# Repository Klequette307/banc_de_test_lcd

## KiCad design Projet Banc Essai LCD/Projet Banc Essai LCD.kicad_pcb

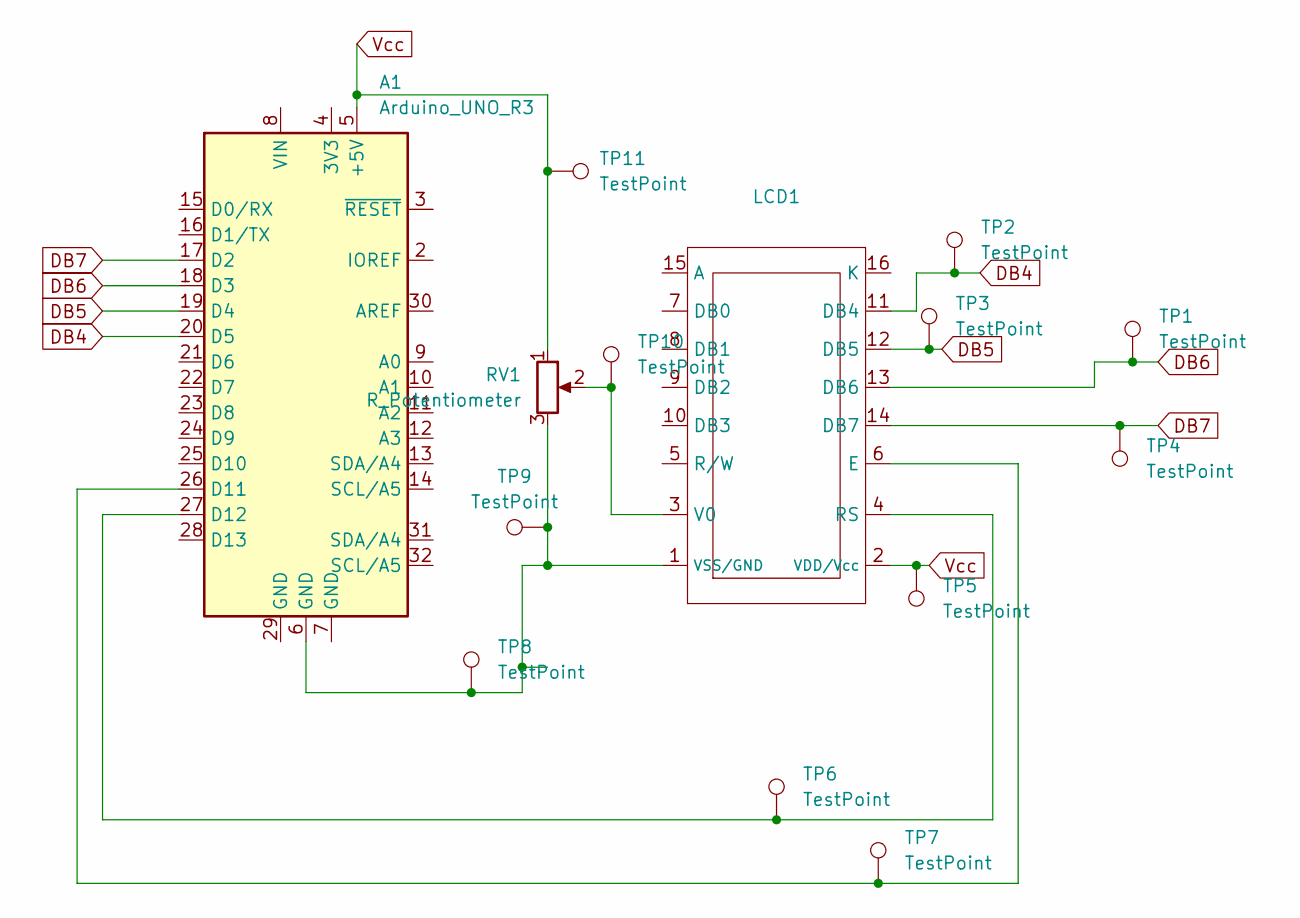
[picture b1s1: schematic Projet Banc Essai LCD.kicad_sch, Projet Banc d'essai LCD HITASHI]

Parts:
A1: Arduino_UNO_R3; Arduino_UNO_R3_WithMountingHoles
LCD1: ecran_hitachi_lcd
RV1: R_Potentiometer; Potentiometer_ACP_CA9-V10_Vertical
TP1, TP2, TP3, TP4, TP5, TP6, TP7, TP8, TP9, TP10, TP11: TestPoint; PinHeader_1x01_P1.00mm_Vertical

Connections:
DB4: A1.20 (D5), LCD1.11 (DB4), TP2.1
DB5: A1.19 (D4), LCD1.12 (DB5), TP3.1
DB6: A1.18 (D3), LCD1.13 (DB6), TP1.1
DB7: A1.17 (D2), LCD1.14 (DB7), TP4.1
unnamed: A1.26 (D11), LCD1.6 (E), TP7.1
unnamed: A1.27 (D12), LCD1.4 (RS), TP6.1
unnamed: LCD1.3 (V0), RV1.2, TP10.1
unnamed: A1.6 (GND), LCD1.1 (VSS/GND), RV1.3, TP8.1, TP9.1
Vcc: A1.5 (+5V), LCD1.2 (VDD/Vcc), RV1.1, TP5.1, TP11.1

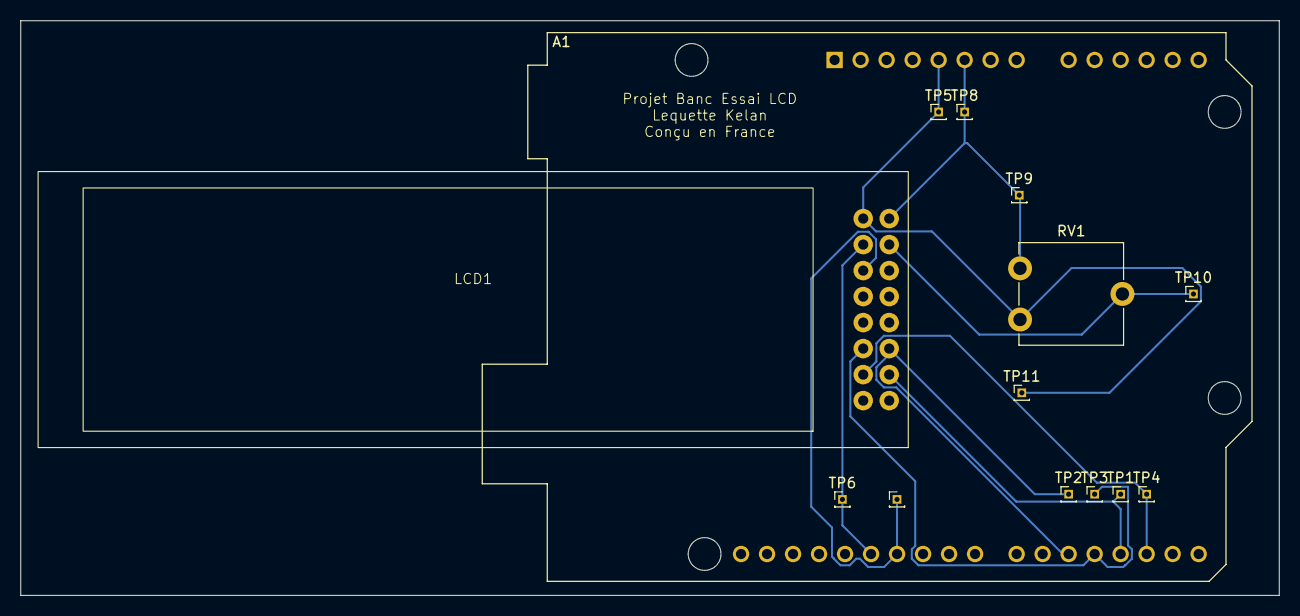
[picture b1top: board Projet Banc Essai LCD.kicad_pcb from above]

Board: 2 copper layers, 122.9 x 56.1 mm, 14 parts (0 on the bottom side), 9 nets.
